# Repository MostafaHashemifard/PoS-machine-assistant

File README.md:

# PoS-machine-assistant
A third-party device to make the payment through PoS machine, more faster and more accurate.

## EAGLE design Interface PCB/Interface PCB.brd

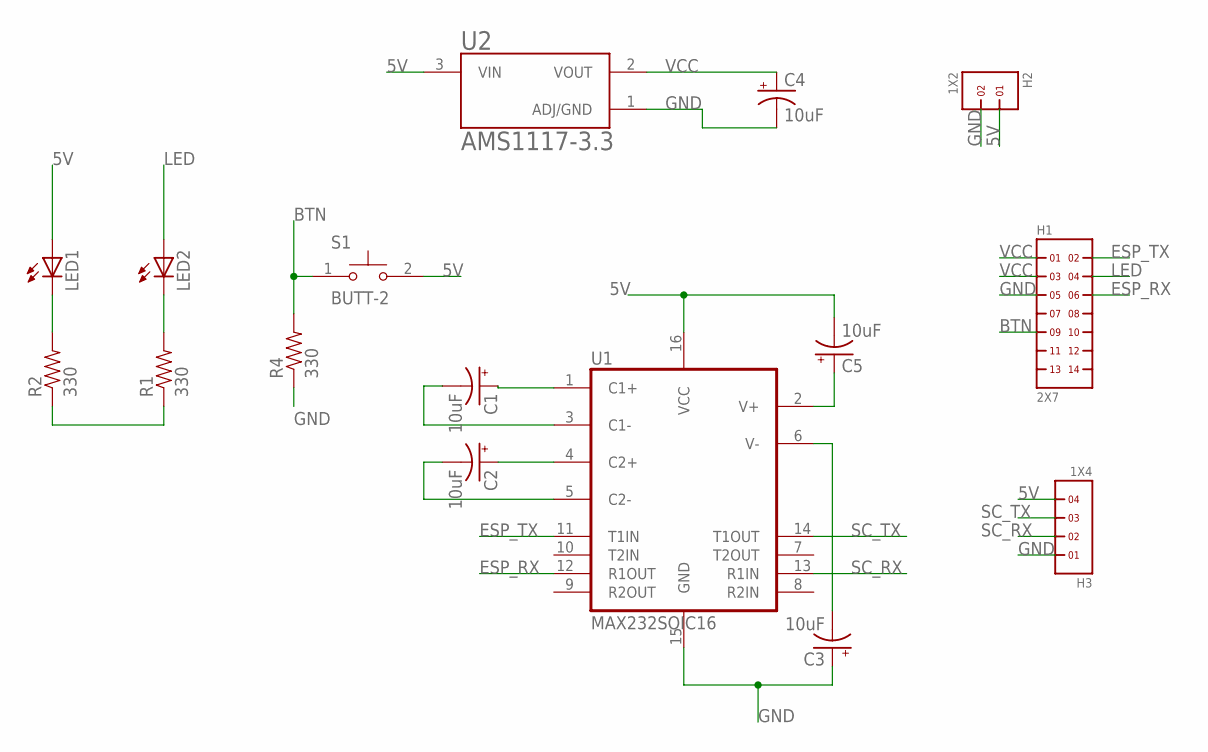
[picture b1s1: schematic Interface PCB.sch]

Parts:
C1, C2, C3, C4, C5: 10uF; EIA3216
H1: 2X7
H2: 1X2
H3: 1X4
LED1, LED2: LED5MM
R1, R2, R4: 330; 0402-RES
S1: BUTT-2; SW_BUTT-2
U1: MAX232SOIC16; SO016
U2: AMS1117-3.3; SOT229P700X180-4N

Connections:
5V: C5.C (-), H2.1, H3.4, LED1.A, S1.2, U1.16 (VCC), U2.3 (VIN)
BTN: H1.9, R4.2, S1.1
ESP_RX: H1.6, U1.12 (R1OUT)
ESP_TX: H1.2, U1.11 (T1IN)
GND: C3.A (+), C4.C (-), H1.5, H2.2, H3.1, R4.1, U1.15 (GND), U2.1 (ADJ/GND)
LED: H1.4, LED2.A
unnamed: C1.A (+), U1.1 (C1+)
unnamed: C1.C (-), U1.3 (C1-)
unnamed: C2.A (+), U1.4 (C2+)
unnamed: C2.C (-), U1.5 (C2-)
unnamed: C3.C (-), U1.6 (V-)
unnamed: C5.A (+), U1.2 (V+)
unnamed: LED1.K (C), R2.2
unnamed: LED2.K (C), R1.2
unnamed: R1.1, R2.1
SC_RX: H3.2, U1.13 (R1IN)
SC_TX: H3.3, U1.14 (T1OUT)
VCC: C4.A (+), H1.1, H1.3, U2.2 (VOUT)

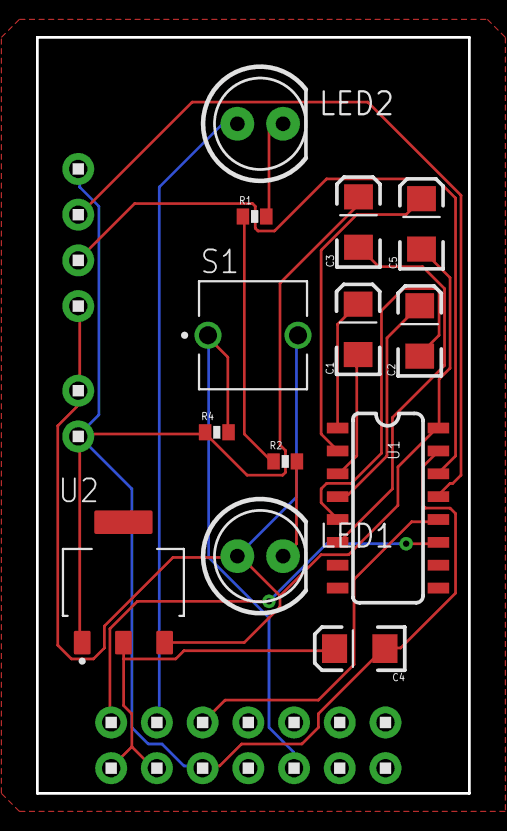
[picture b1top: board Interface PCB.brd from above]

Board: 2 copper layers, 24.0 x 42.0 mm, 16 parts (0 on the bottom side), 18 nets.

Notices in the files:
parts and their libraries:
SparkFun-Capacitors: Licensing: CC v3.0 Share-Alike You are welcome to use this library for commercial purposes.
